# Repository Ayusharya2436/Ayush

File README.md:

Assignment No.09 :- Automatic Night Lamp Controller PCB

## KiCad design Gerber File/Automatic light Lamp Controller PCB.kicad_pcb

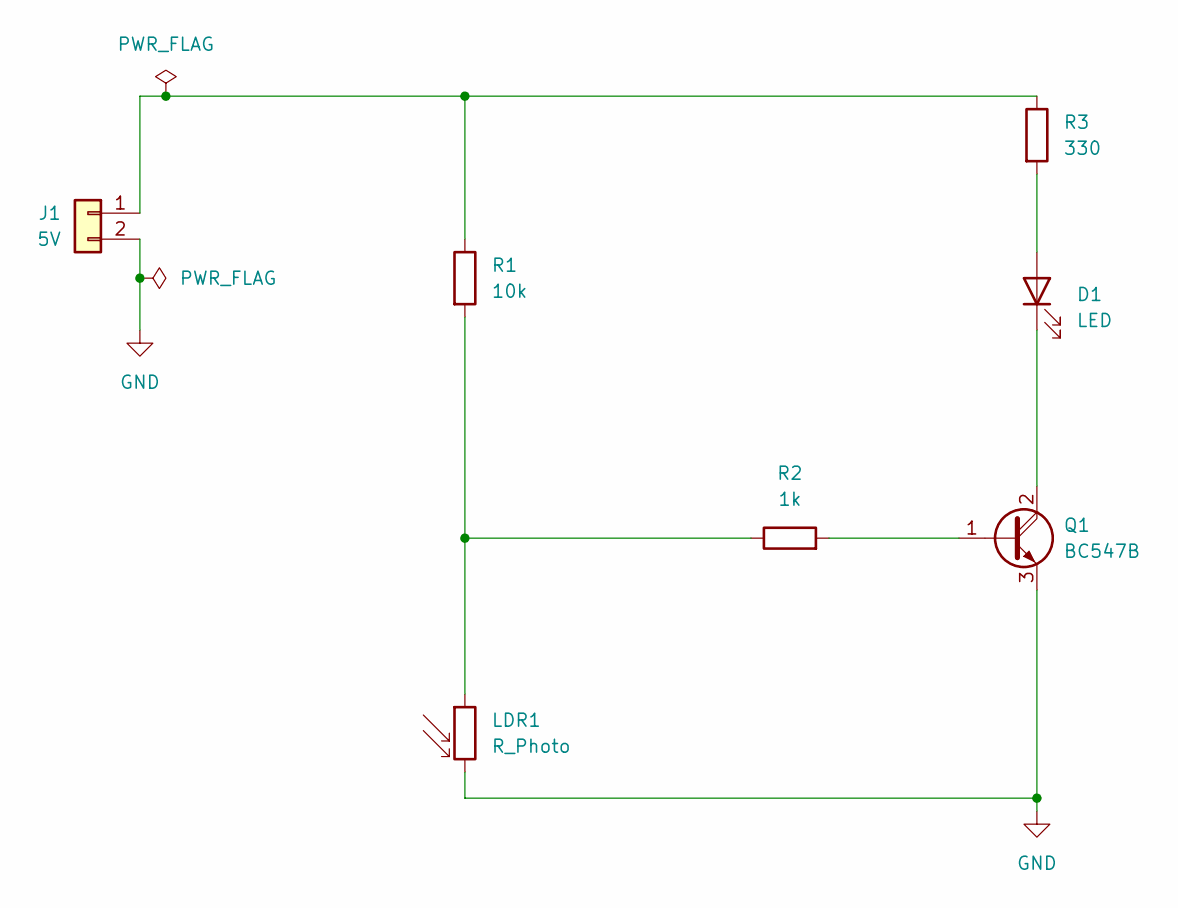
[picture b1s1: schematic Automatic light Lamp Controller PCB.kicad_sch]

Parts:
D1: LED; LED_D5.0mm-3_Horizontal_O3.81mm_Z3.0mm
J1: 5V; PinHeader_1x02_P2.00mm_Vertical
LDR1: R_Photo; R_LDR_4.9x4.2mm_P2.54mm_Vertical
Q1: BC547B; TO-92L_Inline
R1: 10k; R_Axial_DIN0207_L6.3mm_D2.5mm_P10.16mm_Horizontal
R2: 1k; R_Axial_DIN0207_L6.3mm_D2.5mm_P10.16mm_Horizontal
R3: 330; R_Axial_DIN0207_L6.3mm_D2.5mm_P10.16mm_Horizontal

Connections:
GND: J1.2, LDR1.2, Q1.3 (E)
unnamed: D1.2 (A), R3.2
unnamed: D1.1 (K), Q1.2 (C)
unnamed: J1.1, R1.1, R3.1
unnamed: LDR1.1, R1.2, R2.1
unnamed: Q1.1 (B), R2.2

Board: 2 copper layers, 7 parts (0 on the bottom side), 6 nets, no tracks yet.
